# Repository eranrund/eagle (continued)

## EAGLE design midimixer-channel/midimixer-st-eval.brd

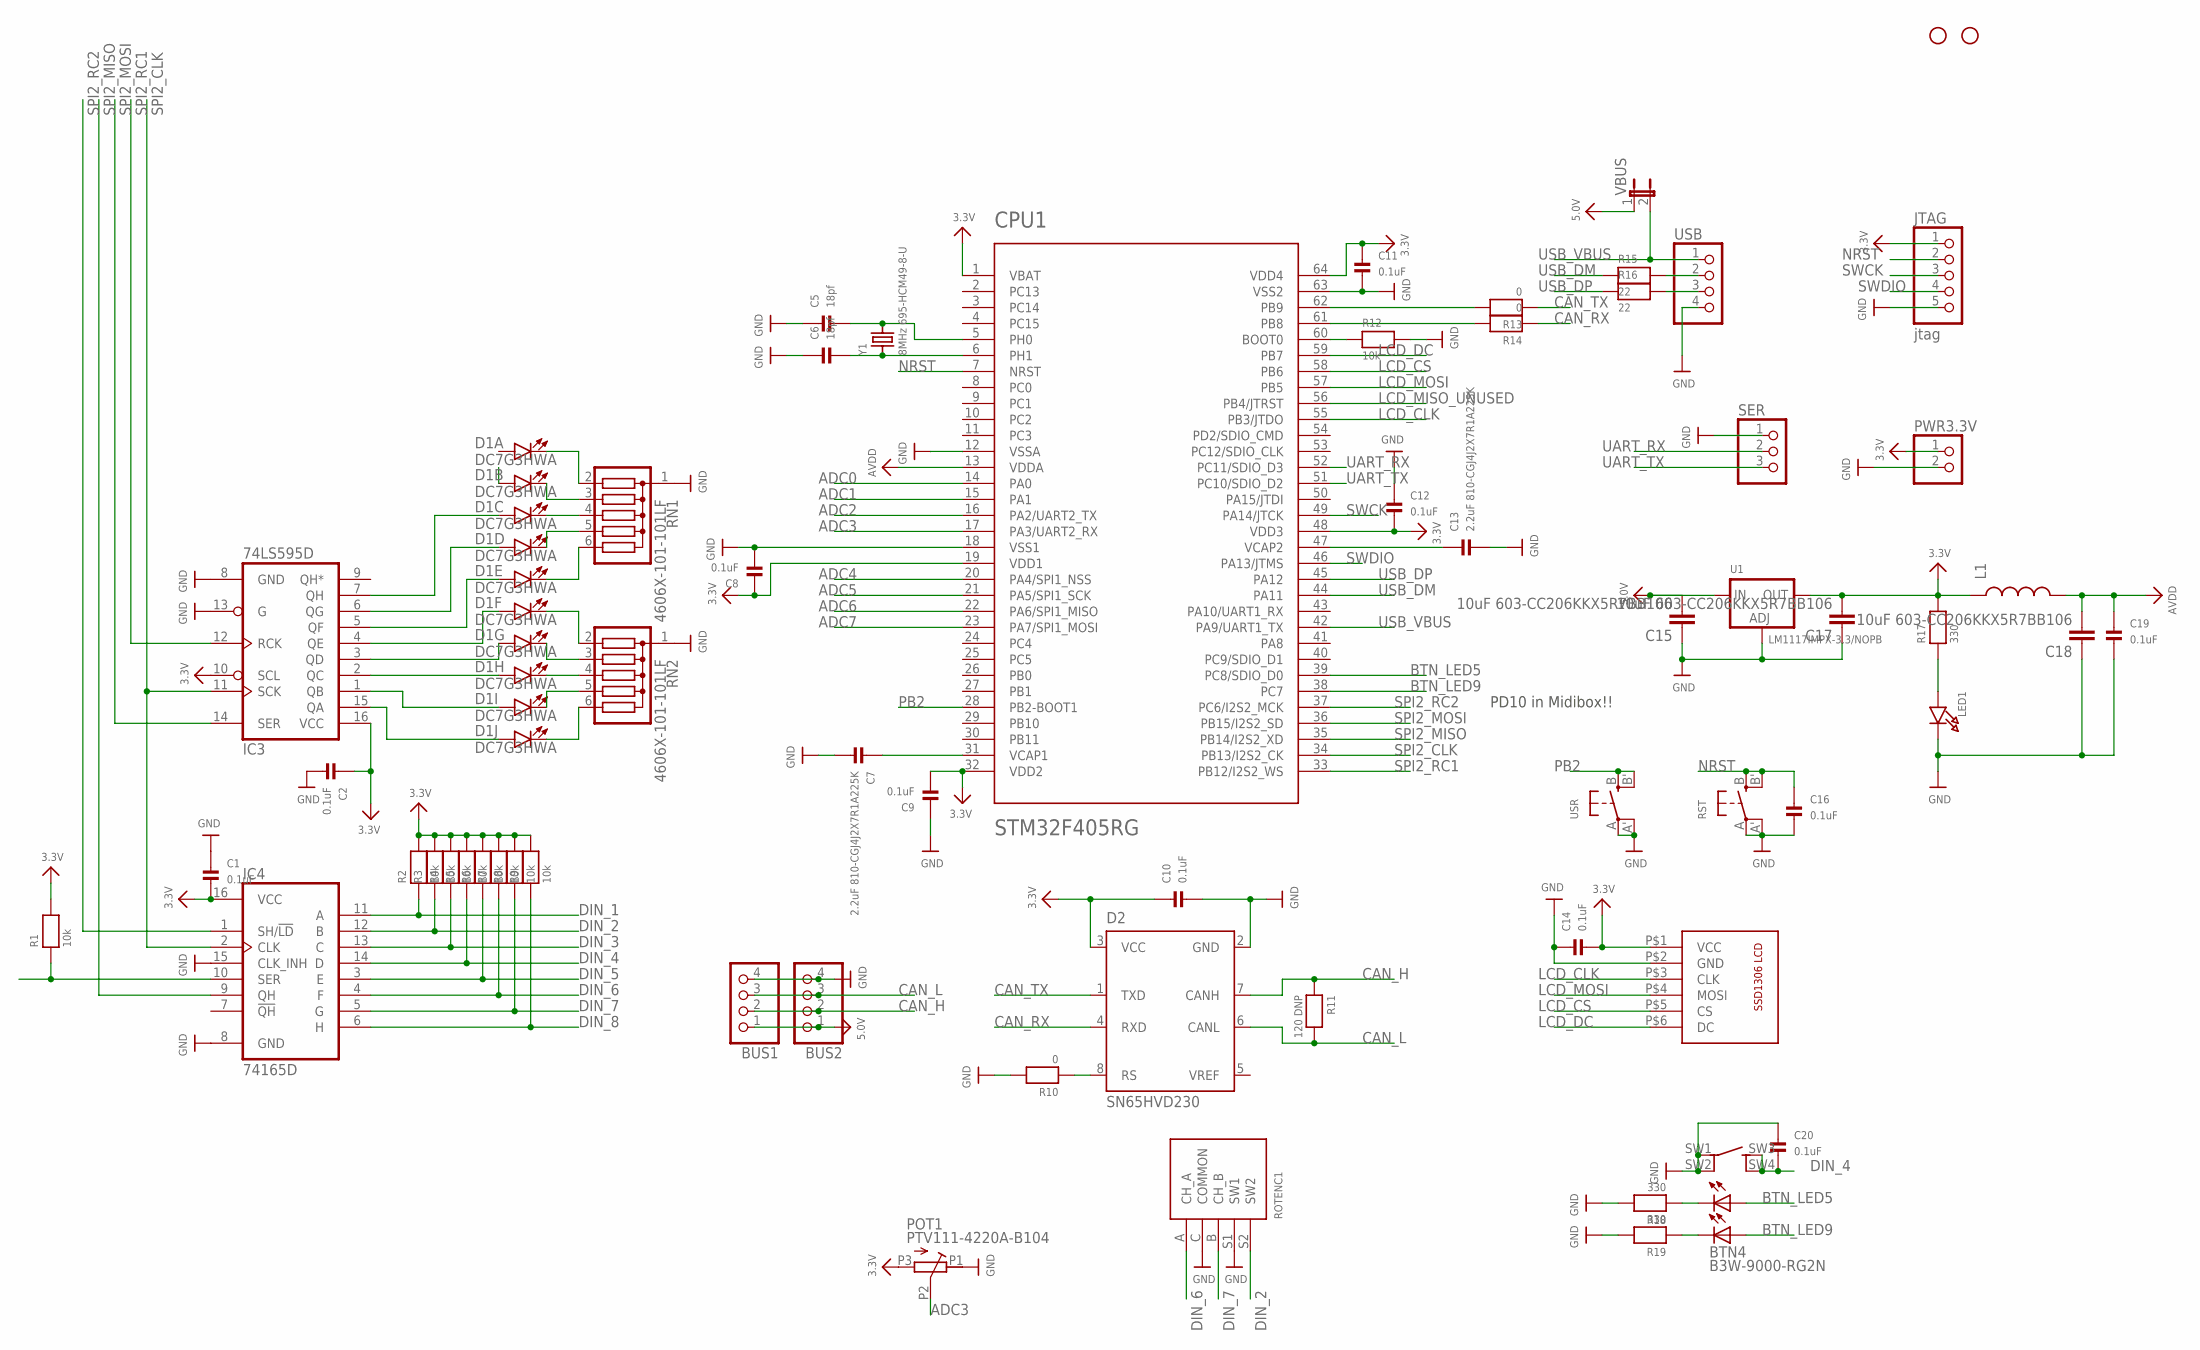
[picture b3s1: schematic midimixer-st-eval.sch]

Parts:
BTN4: B3W-9000-RG2N; B3W-9000-X2X
BUS1, BUS2: HEADER-1X4ROUND; 1X04_ROUND
C1, C2, C8, C9, C10, C11, C12, C14, C16, C19, C20: 0.1uF; 0603
C5, C6: 18pf; 0603
C7, C13: 2.2uF 810-CGJ4J2X7R1A225K; 0805
C15, C17, C18: 10uF 603-CC206KKX5R7BB106; 1206
CPU1: STM32F405RG; TQFP64
D1: DC7G3HWA; LED_BARGAPH_10
D2: SN65HVD230; SO8
H1, H3: STAND-OFF
IC3: 74LS595D; SO16
IC4: 74165D; SO16
JTAG: jtag; 1X05_ROUND_76
L1: INDUCTOR0805; 0805
LCD1: SSD1306-ALI
LED1: LED0603; CHIPLED_0603
POT1: PTV111-4220A-B104; PTV111-4
PWR3.3V: HEADER-1X2ROUND; 1X02_ROUND
R1, R2, R3, R4, R5, R6, R7, R8, R9, R12: 10k; _0603
R10, R13, R14: 0; _0603
R11: 120 DNP; _0603
R15, R16: 22; 0603
R17, R18, R19: 330; 0603
RN1, RN2: 4606X-101-101LF; SIL6
ROTENC1: PEC11-4215K-S0024; PEC111-4XXXK-SXXXX
RST: SWITCH_TACT_SMT; EVQ-Q2
SER: HEADER-1X3ROUND; 1X03_ROUND
U1: LM1117IMPX-3.3/NOPB; SOT223-R
USB: HEADER-1X4ROUND; 1X04_ROUND
USR: SWITCH_TACT_SMT; EVQ-Q2
VBUS: JUMPER2
Y1: 8MHz 695-HCM49-8-U; HC49UP

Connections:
3.3V: C1.2, C2.1, C8.1, C9.2, C10.1, C11.1, C12.2, C14.2, C17.2, CPU1.1 (VBAT), CPU1.19 (VDD1), CPU1.32 (VDD2), CPU1.48 (VDD3), CPU1.64 (VDD4), D2.3 (VCC), IC3.10 (SCL), IC3.16 (VCC), IC4.16 (VCC), JTAG.1, L1.1, LCD1.P$1 (VCC), POT1.P3 (E), PWR3.3V.1, R1.2, R2.2, R3.2, R4.2, R5.2, R6.2, R7.2, R8.2, R9.2, R17.2, U1.2 (OUT)
5.0V: BUS1.1, BUS2.1, C15.2, U1.3 (IN), VBUS.1
ADC0: CPU1.14 (PA0)
ADC1: CPU1.15 (PA1)
ADC2: CPU1.16 (PA2/UART2_TX)
ADC3: CPU1.17 (PA3/UART2_RX), POT1.P2 (S)
ADC4: CPU1.20 (PA4/SPI1_NSS)
ADC5: CPU1.21 (PA5/SPI1_SCK)
ADC6: CPU1.22 (PA6/SPI1_MISO)
ADC7: CPU1.23 (PA7/SPI1_MOSI)
AVDD: C18.2, C19.1, CPU1.13 (VDDA), L1.2
BTN_LED5: BTN4.LED1+, CPU1.39 (PC8/SDIO_D0)
BTN_LED9: BTN4.LED2+, CPU1.38 (PC7)
CAN_H: BUS1.2, BUS2.2, D2.7 (CANH), R11.1
CAN_L: BUS1.3, BUS2.3, D2.6 (CANL), R11.2
CAN_RX: D2.4 (RXD), R14.1
CAN_TX: D2.1 (TXD), R13.1
DIN_1: IC4.11 (A), R2.1
DIN_2: IC4.12 (B), R3.1, ROTENC1.S2 (SW2)
DIN_3: IC4.13 (C), R4.1
DIN_4: BTN4.SW3 (SW2_A), BTN4.SW4 (SW2_B), C20.2, IC4.14 (D), R5.1
DIN_5: IC4.3 (E), R6.1
DIN_6: IC4.4 (F), R7.1, ROTENC1.A (CH_A)
DIN_7: IC4.5 (G), R8.1, ROTENC1.B (CH_B)
DIN_8: IC4.6 (H), R9.1
GND: BTN4.SW1 (SW1_A), BTN4.SW2 (SW1_B), BUS1.4, BUS2.4, C1.1, C2.2, C5.1, C6.1, C7.2, C8.2, C9.1, C10.2, C11.2, C12.1, C13.2, C14.1, C15.1, C16.2, C17.1, C18.1, C19.2, C20.1, CPU1.12 (VSSA), CPU1.18 (VSS1), CPU1.63 (VSS2), D2.2 (GND), IC3.8 (GND), IC3.13 (G), IC4.8 (GND), IC4.15 (CLK_INH), JTAG.5, LCD1.P$2 (GND), LED1.C, POT1.P1 (A), PWR3.3V.2, R10.2, R12.2, R18.2, R19.2, RN1.1, RN2.1, ROTENC1.C (COMMON), ROTENC1.S1 (SW1), RST.A, RST.A' (P1), SER.1, U1.1 (ADJ), USB.4, USR.A, USR.A' (P1)
LCD_CLK: CPU1.55 (PB3/JTDO), LCD1.P$3 (CLK)
LCD_CS: CPU1.58 (PB6), LCD1.P$5 (CS)
LCD_DC: CPU1.59 (PB7), LCD1.P$6 (DC)
LCD_MISO_UNUSED: CPU1.56 (PB4/JTRST)
LCD_MOSI: CPU1.57 (PB5), LCD1.P$4 (MOSI)
unnamed: C6.2, CPU1.6 (PH1), Y1.1
unnamed: C5.2, CPU1.5 (PH0), Y1.2
unnamed: C13.1, CPU1.47 (VCAP2)
unnamed: C7.1, CPU1.31 (VCAP1)
unnamed: LED1.A, R17.1
unnamed: CPU1.60 (BOOT0), R12.1
unnamed: R15.2, USB.2
unnamed: R16.2, USB.3
unnamed: BTN4.LED1-, R18.1
unnamed: BTN4.LED2-, R19.1
unnamed: CPU1.62 (PB9), R13.2
unnamed: D1.20 (C), RN1.2
unnamed: D1.19 (C), RN1.3
unnamed: D1.18 (C), RN1.4
unnamed: D1.17 (C), RN1.5
unnamed: D1.16 (C), RN1.6
unnamed: D1.15 (C), RN2.2
unnamed: D1.14 (C), RN2.3
unnamed: D1.13 (C), RN2.4
unnamed: D1.12 (C), RN2.5
unnamed: D1.11 (C), RN2.6
unnamed: CPU1.61 (PB8), R14.2
unnamed: IC4.10 (SER), R1.1
unnamed: D1.10 (A), IC3.15 (QA)
unnamed: D1.9 (A), IC3.1 (QB)
unnamed: D1.8 (A), IC3.2 (QC)
unnamed: D1.7 (A), IC3.3 (QD)
unnamed: D1.6 (A), IC3.4 (QE)
unnamed: D1.5 (A), IC3.5 (QF)
unnamed: D1.4 (A), IC3.6 (QG)
unnamed: D1.3 (A), IC3.7 (QH)
unnamed: D2.8 (RS), R10.1
NRST: C16.1, CPU1.7 (NRST), JTAG.2, RST.B (S), RST.B' (S1)
PB2: CPU1.28 (PB2-BOOT1), USR.B (S), USR.B' (S1)
SPI2_CLK: CPU1.34 (PB13/I2S2_CK), IC3.11 (SCK), IC4.2 (CLK)
SPI2_MISO: CPU1.35 (PB14/I2S2_XD), IC4.9 (QH)
SPI2_MOSI: CPU1.36 (PB15/I2S2_SD), IC3.14 (SER)
SPI2_RC1: CPU1.33 (PB12/I2S2_WS), IC3.12 (RCK)
SPI2_RC2: CPU1.37 (PC6/I2S2_MCK), IC4.1 (SH/!LD)
SWCK: CPU1.49 (PA14/JTCK), JTAG.3
SWDIO: CPU1.46 (PA13/JTMS), JTAG.4
UART_RX: CPU1.52 (PC11/SDIO_D3), SER.2
UART_TX: CPU1.51 (PC10/SDIO_D2), SER.3
USB_DM: CPU1.44 (PA11), R15.1
USB_DP: CPU1.45 (PA12), R16.1
USB_VBUS: CPU1.42 (PA9/UART1_TX), USB.1, VBUS.2

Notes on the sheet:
PD10 in Midibox!!

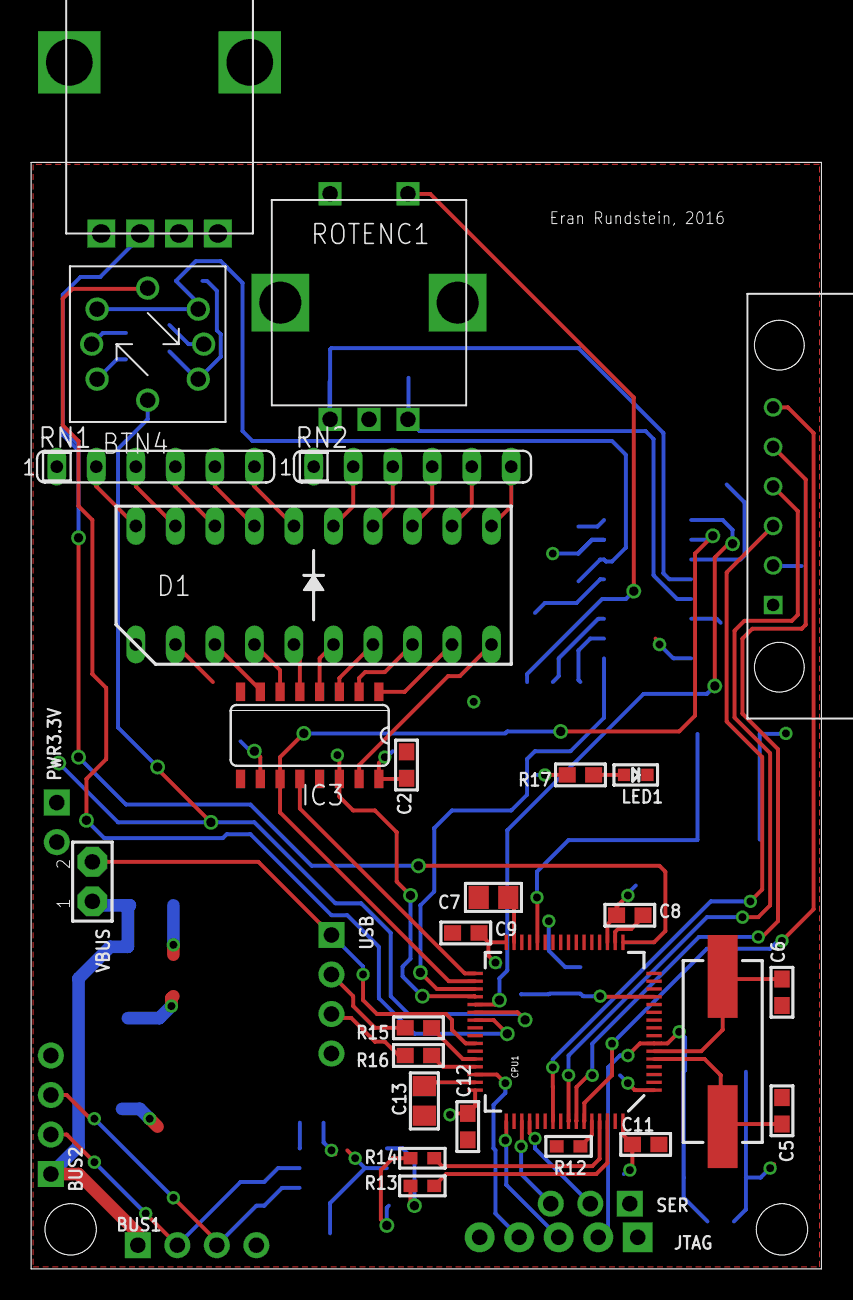
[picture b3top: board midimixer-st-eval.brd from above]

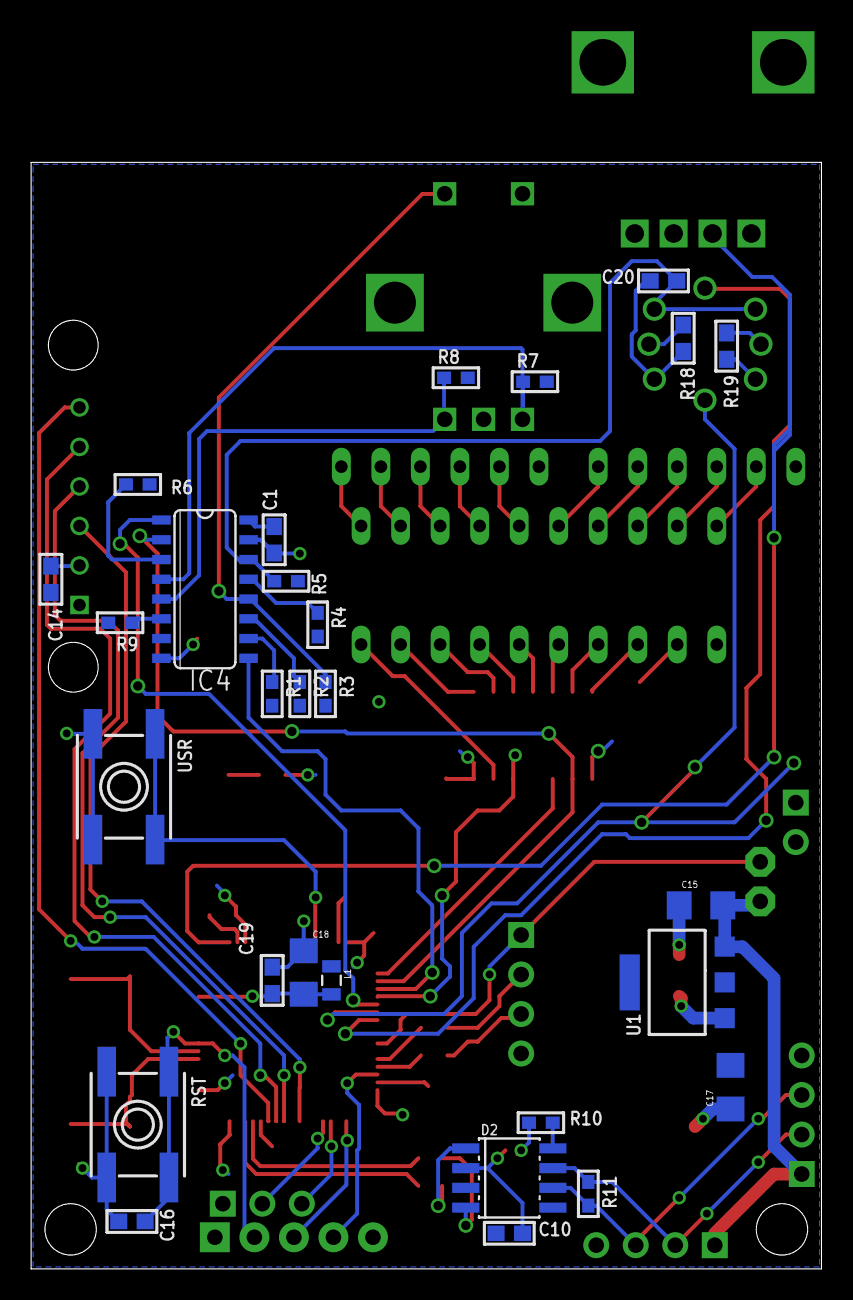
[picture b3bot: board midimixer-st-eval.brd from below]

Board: 2 copper layers, 50.8 x 71.1 mm, 63 parts (28 on the bottom side), 69 nets.

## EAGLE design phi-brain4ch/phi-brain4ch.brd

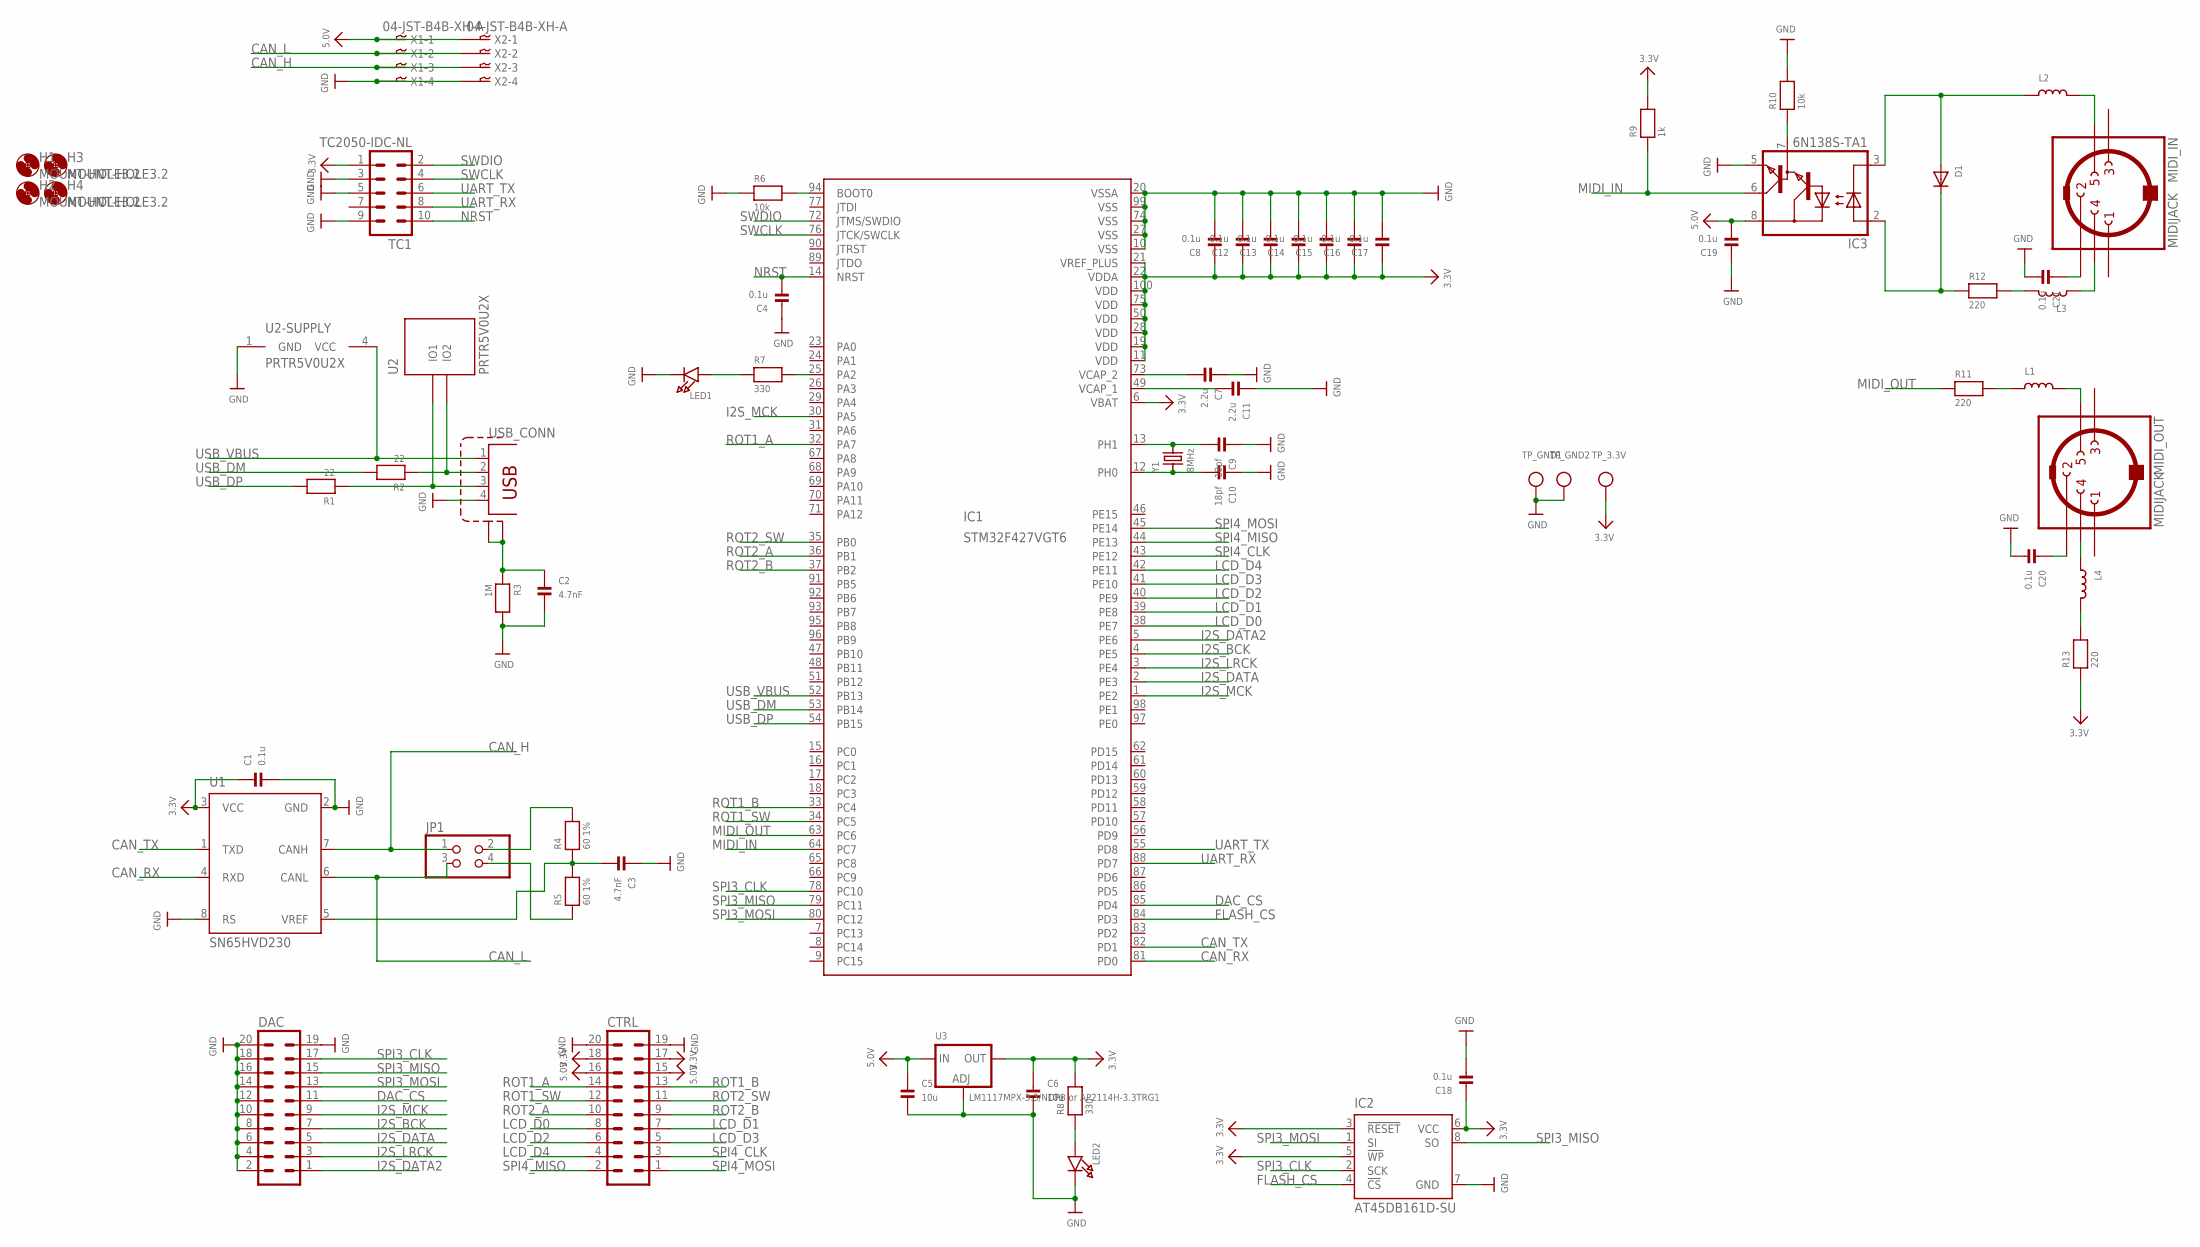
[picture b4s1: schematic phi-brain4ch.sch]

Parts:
C1, C4, C8, C12, C13, C14, C15, C16, C17, C18, C19, C20, C21: 0.1u; 0603; PARTNO 0805DD104KAT2A
C2, C3: 4.7nF; 0805; PARTNO 885012207090
C5, C6: 10u; 0805; PARTNO 81-GRM21BR6YA106KE3L
C7, C11: 2.2u; 0805; PARTNO 581-08053D225MAT2A
C9, C10: 18pf; 0805; PARTNO C0805C180M3GACTU
CTRL: ML20; PARTNO 61202021621
D1: DIODESOD-123; SOD-123; PARTNO MBR120
DAC: ML20; PARTNO 61202021621
H1, H2, H3, H4: MOUNT-HOLE3.2; 3,2
IC1: STM32F427VGT6; TQFP100; PARTNO STM32F427VGT6
IC2: AT45DB161D-SU; 8S2
IC3: 6N138S-TA1; SO8-GW300; PARTNO 6N138S
JP1: PINHD-2X2; 2X02
L1, L2, L3, L4: INDUCTOR0805; 0805; PARTNO 70-ILHB0805ER601V
LED1, LED2: LED0805; CHIPLED_0805; PARTNO 604-APT2012YC
MIDI_IN: MIDIJACK; CP-2350
MIDI_OUT: MIDIJACK; CP-2350
R1, R2: 22; 0805; MPN MF-RES-0603-22
R3: 1M; 0805; PARTNO AS08J1004ET
R4, R5: 60 1%; 0805; MPN MF-RES-0603-60.4
R6, R10: 10k; 0805; PARTNO RC0805FR-0710KL
R7, R8: 330; 0805; MPN MF-RES-0603-330
R9: 1k; 0805; PARTNO AS08J1001ET
R11, R12, R13: 220; 0805; PARTNO ERJ-6GEYJ221V
TC1: TC2050-IDC-NL
TP_3.3V: TESTPOINT0.1"; 1X01_ROUND
TP_GND1, TP_GND2: TESTPOINT0.1"; 1X01_ROUND
U1: SN65HVD230; SO8
U2: PRTR5V0U2X; SOT-143B
U3: LM1117MPX-3.3/NOPB or AP2114H-3.3TRG1; SOT223-R
USB: TE-292304-1
X1, X2: 04-JST-B4B-XH-A; B4B-XH
Y1: 8MHz; HC49UP; PARTNO ABLS2-8.000MHz-B1U-T

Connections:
3.3V: C1.1, C6.1, C8.1, C12.1, C13.1, C14.1, C15.1, C16.1, C17.1, C18.1, CTRL.17, CTRL.18, IC1.6 (VBAT), IC1.11 (VDD), IC1.19 (VDD), IC1.21 (VREF_PLUS), IC1.22 (VDDA), IC1.28 (VDD), IC1.50 (VDD), IC1.75 (VDD), IC1.100 (VDD), IC2.3 (!RESET), IC2.5 (!WP), IC2.6 (VCC), R8.2, R9.2, R13.1, TC1.1, TP_3.3V.1, U1.3 (VCC), U3.2 (OUT); also elsewhere on the board
5.0V: C5.1, C19.2, CTRL.15, CTRL.16, IC3.8 (VCC), U3.3 (IN), X1.P$1, X2.P$1
CAN_H: JP1.1, U1.7 (CANH), X1.P$3, X2.P$3
CAN_L: JP1.3, U1.6 (CANL), X1.P$2, X2.P$2
CAN_RX: IC1.81 (PD0), U1.4 (RXD)
CAN_TX: IC1.82 (PD1), U1.1 (TXD)
DAC_CS: DAC.11, IC1.85 (PD4)
FLASH_CS: IC1.84 (PD3), IC2.4 (!CS)
GND: C1.2, C2.2, C3.1, C4.1, C5.2, C6.2, C7.1, C8.2, C9.1, C10.1, C11.1, C12.2, C13.2, C14.2, C15.2, C16.2, C17.2, C18.2, C19.1, C20.2, C21.2, CTRL.19, CTRL.20, DAC.2, DAC.4, DAC.6, DAC.8, DAC.10, DAC.12, DAC.14, DAC.16, DAC.18, DAC.19, DAC.20, IC1.10 (VSS), IC1.20 (VSSA), IC1.27 (VSS), IC1.74 (VSS), IC1.99 (VSS), IC2.7 (GND), IC3.5 (GND), LED1.C, LED2.C, R3.2, R6.1, R10.2, TC1.3, TC1.5, TC1.9, TP_GND1.1, TP_GND2.1, U1.2 (GND), U1.8 (RS), U2.1 (GND), U3.1 (ADJ), USB.4, X1.P$4, X2.P$4; also elsewhere on the board
I2S_BCK: DAC.7, IC1.4 (PE5)
I2S_CKIN: IC1.66 (PC9); also elsewhere on the board
I2S_DATA: DAC.5, IC1.2 (PE3)
I2S_DATA2: DAC.1, IC1.5 (PE6)
I2S_LRCK: DAC.3, IC1.3 (PE4)
I2S_MCK: DAC.9, IC1.1 (PE2), IC1.30 (PA5)
LCD_D0: CTRL.8, IC1.38 (PE7)
LCD_D1: CTRL.7, IC1.39 (PE8)
LCD_D2: CTRL.6, IC1.40 (PE9)
LCD_D3: CTRL.5, IC1.41 (PE10)
LCD_D4: CTRL.4, IC1.42 (PE11)
MIDI_IN: IC1.64 (PC7), IC3.6 (VO), R9.1
MIDI_OUT: IC1.63 (PC6), R11.1
unnamed: IC1.94 (BOOT0), R6.2
unnamed: C11.2, IC1.49 (VCAP_1)
unnamed: C7.2, IC1.73 (VCAP_2)
unnamed: C9.2, IC1.13 (PH1), Y1.2
unnamed: C10.2, IC1.12 (PH0), Y1.1
unnamed: LED2.A, R8.1
unnamed: JP1.2, R4.2
unnamed: JP1.4, R5.1
unnamed: C3.2, R4.1, R5.2, U1.5 (VREF)
unnamed: IC1.25 (PA2), R7.2
unnamed 32: IC1.23 (PA0); also elsewhere on the board
unnamed: LED1.A, R7.1
unnamed: L1.2, MIDI_OUT.5
unnamed: L1.1, R11.2
unnamed: L3.1, MIDI_IN.4
unnamed: D1.C, IC3.2 (A), R12.1
unnamed: R2.1, U2.3 (IO2), USB.2
unnamed: R1.1, U2.2 (IO1), USB.3
unnamed: C2.1, R3.1, USB.P$1 (S1), USB.P$2 (S2)
unnamed: D1.A, IC3.3 (C), L2.1
unnamed: IC3.7 (VB), R10.1
unnamed: C20.1, MIDI_OUT.2
unnamed: C21.1, MIDI_IN.2
unnamed: L2.2, MIDI_IN.5
unnamed: L3.2, R12.2
unnamed: L4.2, R13.2
unnamed: L4.1, MIDI_OUT.4
NRST: C4.2, IC1.14 (NRST), TC1.10
ROT1_A: CTRL.14, IC1.32 (PA7)
ROT1_B: CTRL.13, IC1.33 (PC4)
ROT1_SW: CTRL.12, IC1.34 (PC5)
ROT2_A: CTRL.10, IC1.36 (PB1)
ROT2_B: CTRL.9, IC1.37 (PB2)
ROT2_SW: CTRL.11, IC1.35 (PB0)
SPI3_CLK: DAC.17, IC1.78 (PC10), IC2.2 (SCK)
SPI3_MISO: DAC.15, IC1.79 (PC11), IC2.8 (SO)
SPI3_MOSI: DAC.13, IC1.80 (PC12), IC2.1 (SI)
SPI4_CLK: CTRL.3, IC1.43 (PE12)
SPI4_MISO: CTRL.2, IC1.44 (PE13)
SPI4_MOSI: CTRL.1, IC1.45 (PE14)
SWCLK: IC1.76 (JTCK/SWCLK), TC1.4
SWDIO: IC1.72 (JTMS/SWDIO), TC1.2
UART_RX: IC1.87 (PD6), IC1.88 (PD7), TC1.8
UART_TX: IC1.55 (PD8), IC1.86 (PD5), TC1.6
USB_DM: IC1.53 (PB14), R2.2
USB_DP: IC1.54 (PB15), R1.2
USB_VBUS: IC1.52 (PB13), U2.4 (VCC), USB.1

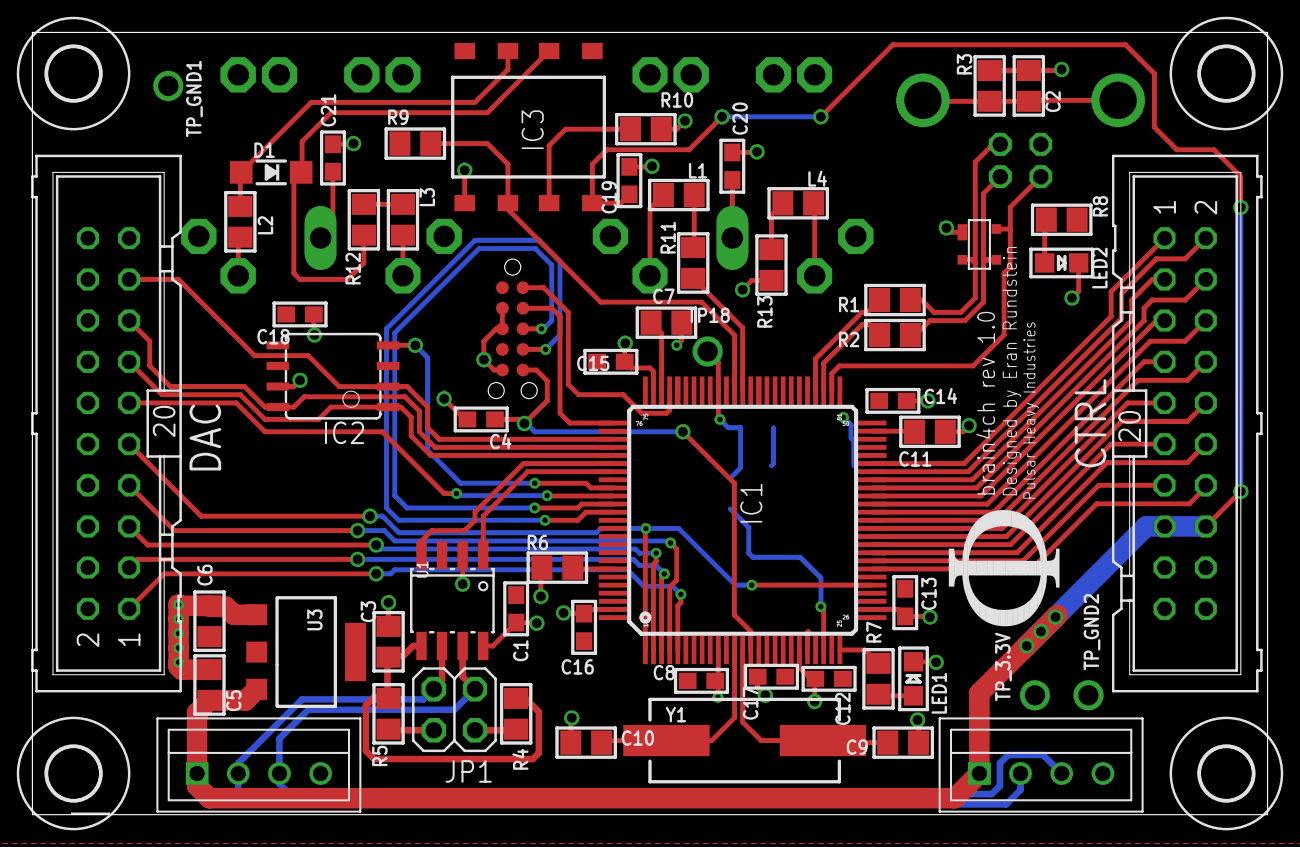
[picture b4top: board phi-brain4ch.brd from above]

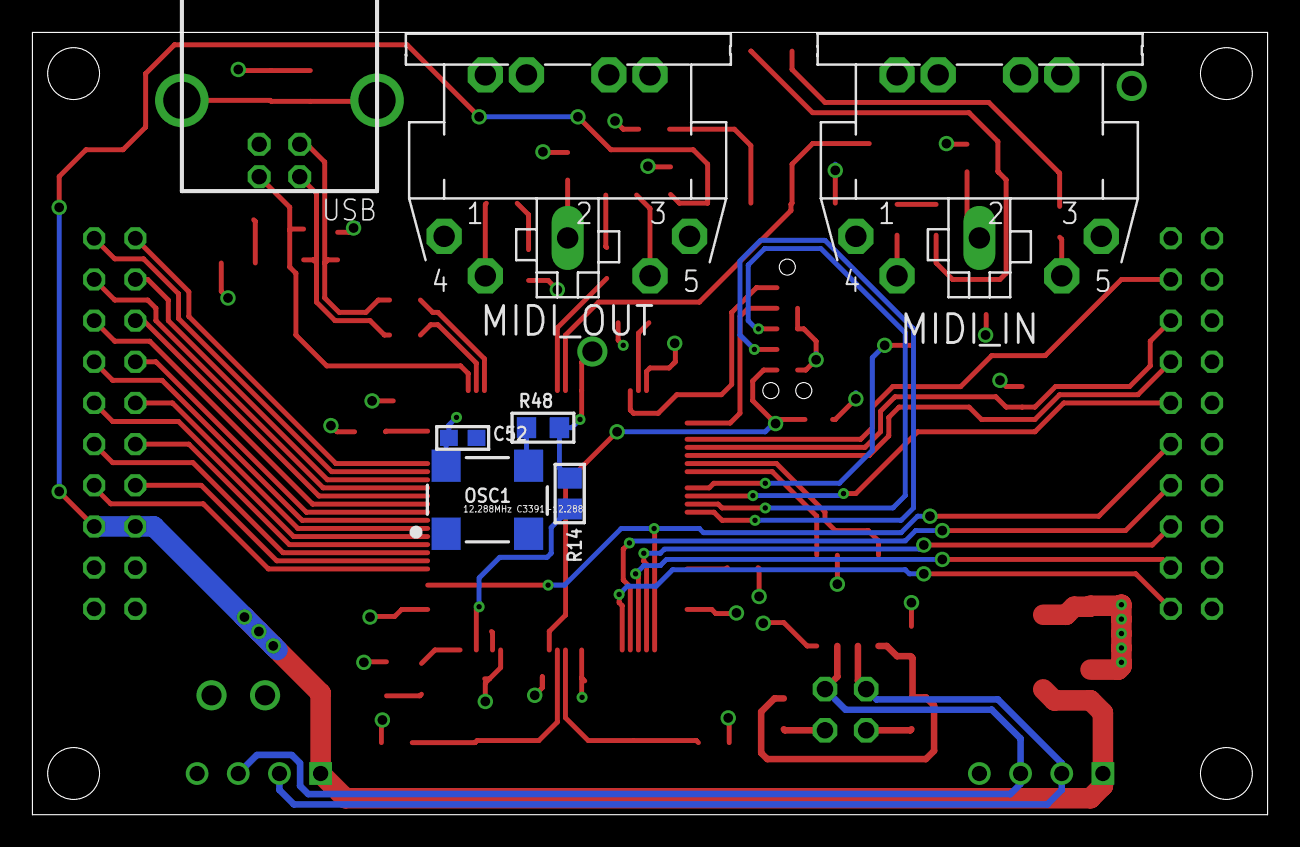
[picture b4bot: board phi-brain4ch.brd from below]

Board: 2 copper layers, 76.2 x 48.3 mm, 69 parts (7 on the bottom side), 70 nets.

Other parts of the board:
C52: 0.1u; 0603
OSC1: 12.288MHz C3391-12.288; OSC_7X5MM
R14: 0; 0805
R48: 0; _0805
TP18: 1X01_ROUND

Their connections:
3.3V: C52.1, OSC1.4; also elsewhere on the board
GND: C52.2, OSC1.2; also elsewhere on the board
I2S_CKIN: R14.1, R48.2, TP18.1; also elsewhere on the board
unnamed 32: R14.2; also elsewhere on the board
unnamed: OSC1.3, R48.1

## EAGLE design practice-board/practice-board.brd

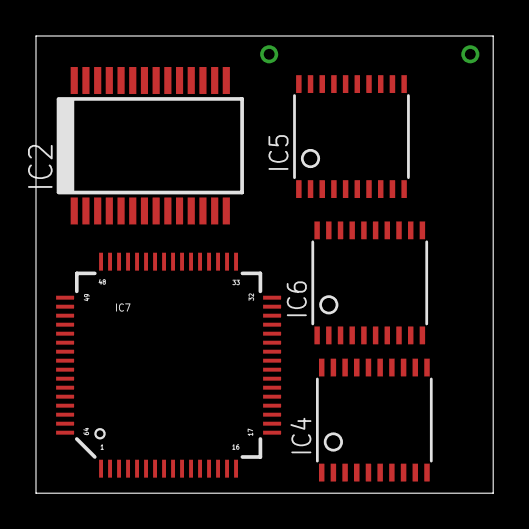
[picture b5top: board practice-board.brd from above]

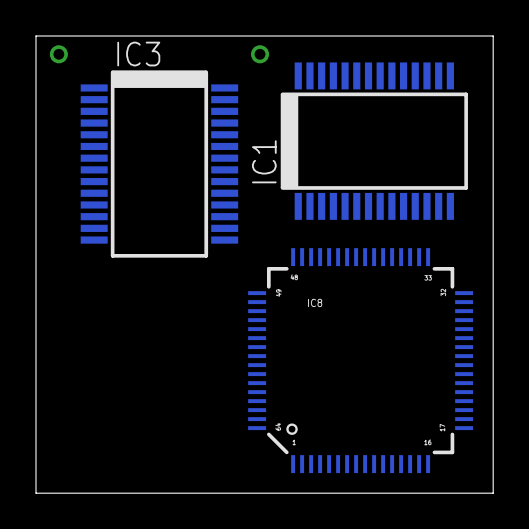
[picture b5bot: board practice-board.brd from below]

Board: 2 copper layers, 25.4 x 25.4 mm, 8 parts (3 on the bottom side), 4 nets, no tracks yet.

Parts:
IC1, IC2, IC3: PCM1792A; SSOP28
IC4, IC5, IC6: PCM5102; TSSOP20
IC7, IC8: STM32F302_F303_B_C_LQFP64; TQFP64

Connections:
VDD: IC7.19, IC7.32, IC7.48, IC7.64, IC8.19, IC8.32, IC8.48, IC8.64
VDDA: IC7.13, IC8.13
VSS: IC7.31, IC7.47, IC7.63, IC8.31, IC8.47, IC8.63
VSSA: IC7.12, IC8.12

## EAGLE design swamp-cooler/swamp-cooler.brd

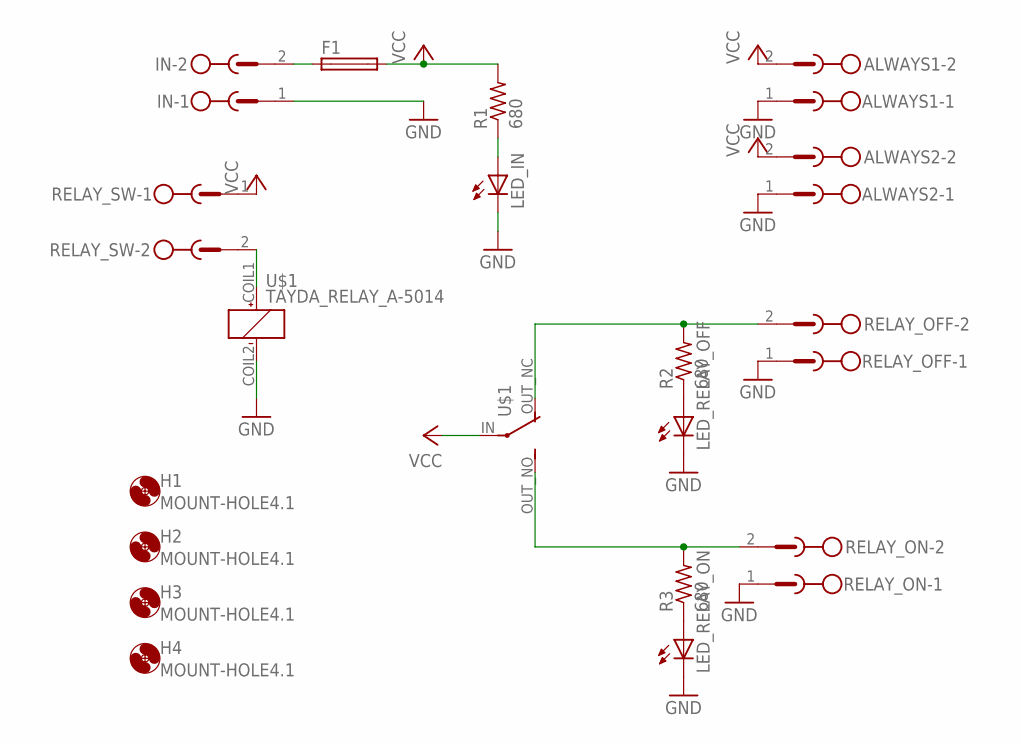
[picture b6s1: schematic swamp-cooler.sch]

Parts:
ALWAYS1, ALWAYS2: MSTBV2
F1: SH22,5A
H1, H2, H3, H4: MOUNT-HOLE4.1; 4,1
IN: MSTBV2
LED_IN: LED5MM
LED_RELAY_OFF: LED5MM
LED_RELAY_ON: LED5MM
R1, R2, R3: 680; 0204/7
RELAY_OFF: MSTBV2
RELAY_ON: MSTBV2
RELAY_SW: MSTBV2
U$1: TAYDA_RELAY_A-5014

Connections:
GND: ALWAYS1.1, ALWAYS2.1, IN.1, LED_IN.K (C), LED_RELAY_OFF.K (C), LED_RELAY_ON.K (C), RELAY_OFF.1, RELAY_ON.1, U$1.COIL2 (-)
unnamed: LED_IN.A, R1.1
unnamed: LED_RELAY_OFF.A, R2.1
unnamed: R2.2, RELAY_OFF.2, U$1.OUT_NC (NC)
unnamed: LED_RELAY_ON.A, R3.1
unnamed: R3.2, RELAY_ON.2, U$1.OUT_NO (NO)
unnamed: F1.1, IN.2
unnamed: RELAY_SW.2, U$1.COIL1 (+)
VCC: ALWAYS1.2, ALWAYS2.2, F1.2, R1.2, RELAY_SW.1, U$1.IN

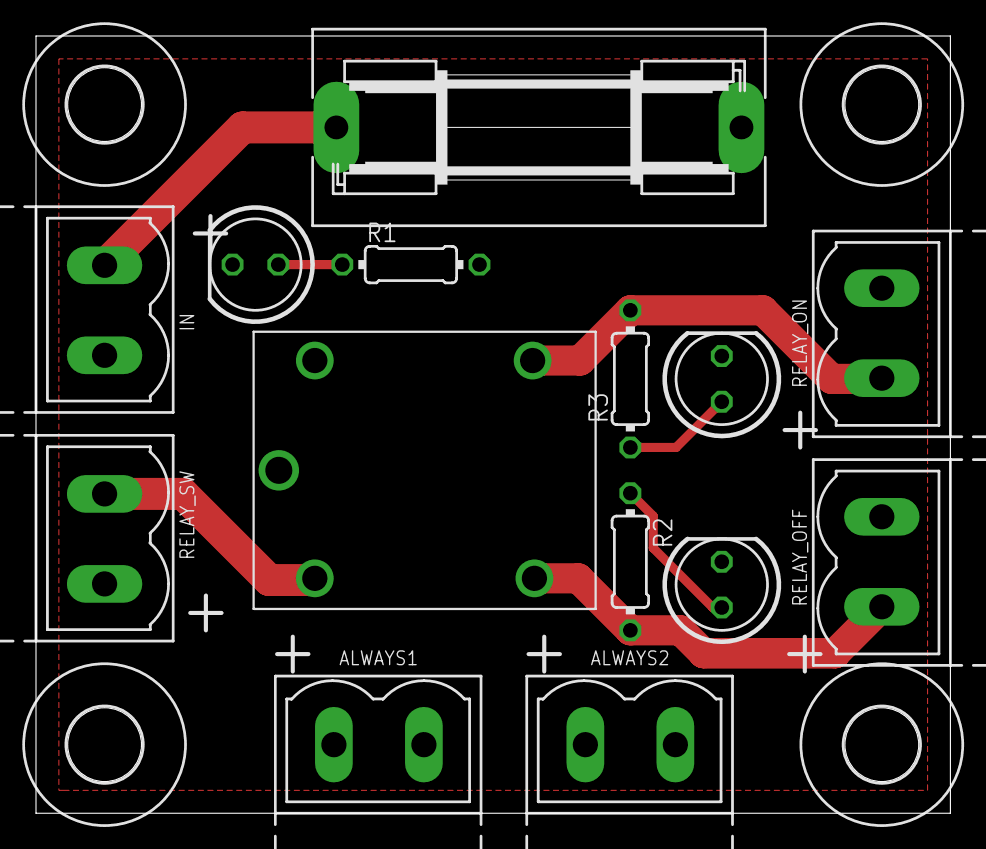
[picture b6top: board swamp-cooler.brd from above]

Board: 2 copper layers, 50.8 x 43.2 mm, 18 parts (0 on the bottom side), 9 nets.
